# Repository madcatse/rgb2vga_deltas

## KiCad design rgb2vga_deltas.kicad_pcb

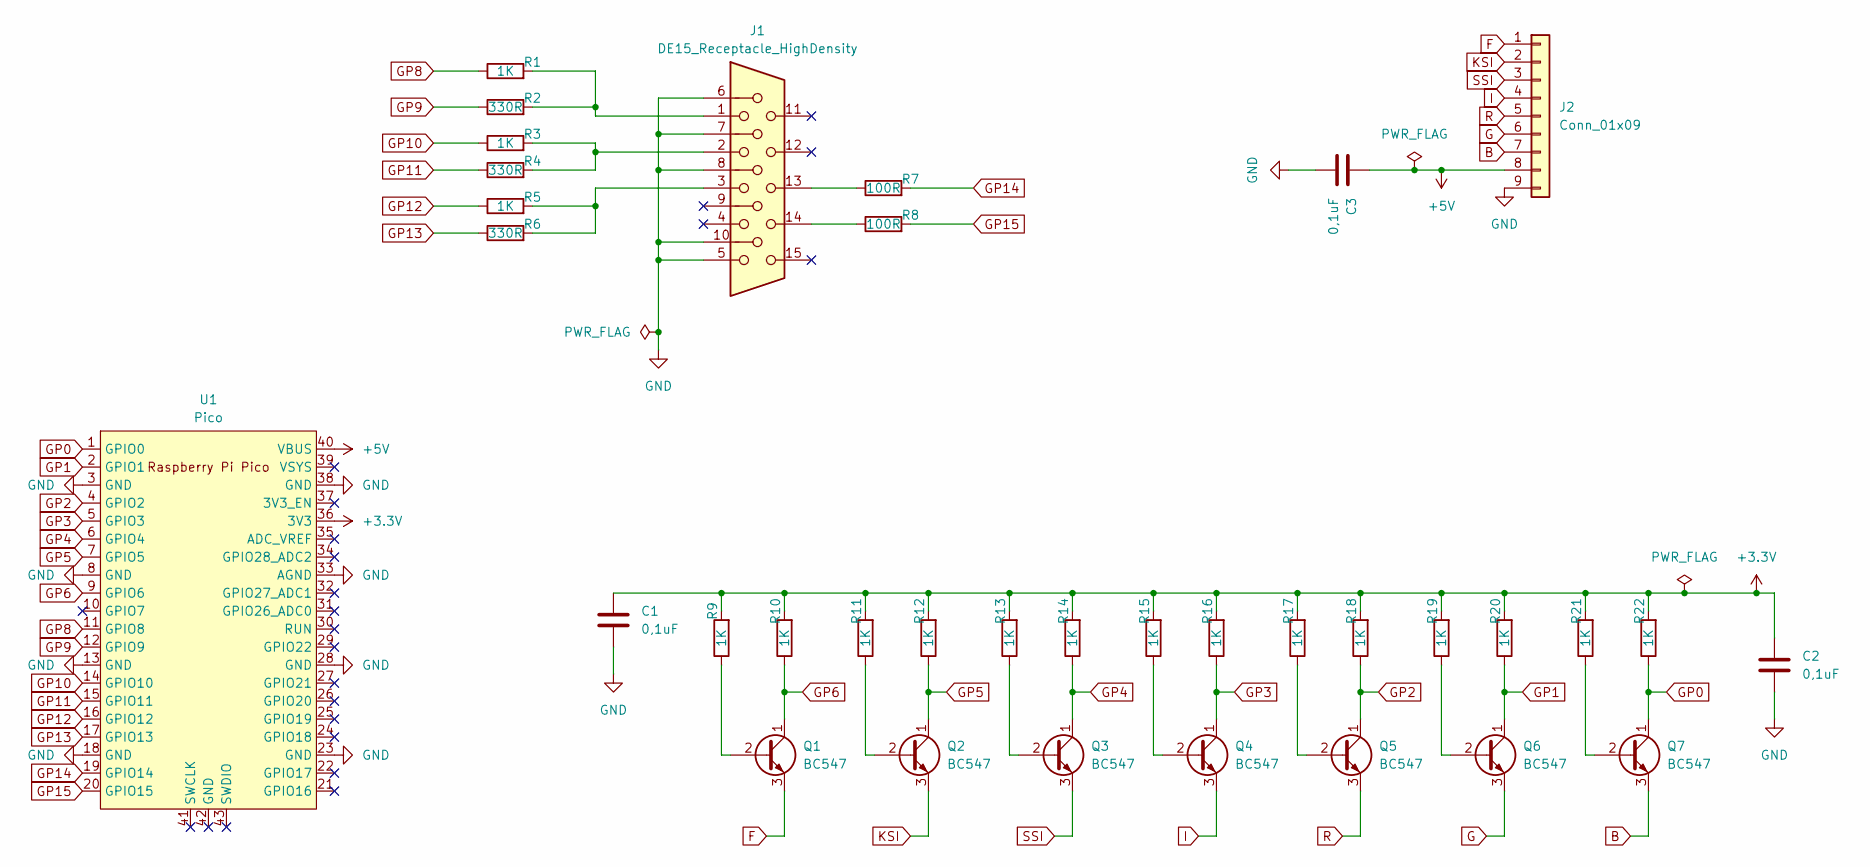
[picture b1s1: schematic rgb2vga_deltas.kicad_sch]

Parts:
C1, C2, C3: 0,1uF; C_Disc_D7.0mm_W2.5mm_P5.00mm
J1: DE15_Receptacle_HighDensity; DSUB-15-HD_Female_Horizontal_P2.29x1.98mm_EdgePinOffset3.03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
J2: Conn_01x09; PinHeader_1x09_P2.54mm_Vertical
Q1, Q2, Q3, Q4, Q5, Q6, Q7: BC547; TO-92_Inline
R1, R3, R5, R9, R10, R11, R12, R13, R14, R15, R16, R17, R18, R19, R20, R21, R22: 1K; R_Axial_DIN0207_L6.3mm_D2.5mm_P10.16mm_Horizontal
R2, R4, R6: 330R; R_Axial_DIN0207_L6.3mm_D2.5mm_P10.16mm_Horizontal
R7, R8: 100R; R_Axial_DIN0207_L6.3mm_D2.5mm_P10.16mm_Horizontal
U1: Pico; RPi_Pico_SMD_TH

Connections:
+3.3V: C1.1, C2.1, R9.2, R10.2, R11.2, R12.2, R13.2, R14.2, R15.2, R16.2, R17.2, R18.2, R19.2, R20.2, R21.2, R22.2, U1.36 (3V3)
+5V: C3.1, J2.8, U1.40 (VBUS)
B: J2.7, Q7.3 (E)
F: J2.1, Q1.3 (E)
G: J2.6, Q6.3 (E)
GND: C1.2, C2.2, C3.2, J1.5, J1.6, J1.7, J1.8, J1.10, J2.9, U1.3 (GND), U1.8 (GND), U1.13 (GND), U1.18 (GND), U1.23 (GND), U1.28 (GND), U1.33 (AGND), U1.38 (GND)
GP0: Q7.1 (C), R22.1, U1.1 (GPIO0)
GP1: Q6.1 (C), R20.1, U1.2 (GPIO1)
GP2: Q5.1 (C), R18.1, U1.4 (GPIO2)
GP3: Q4.1 (C), R16.1, U1.5 (GPIO3)
GP4: Q3.1 (C), R14.1, U1.6 (GPIO4)
GP5: Q2.1 (C), R12.1, U1.7 (GPIO5)
GP6: Q1.1 (C), R10.1, U1.9 (GPIO6)
GP8: R1.1, U1.11 (GPIO8)
GP9: R2.1, U1.12 (GPIO9)
GP10: R3.1, U1.14 (GPIO10)
GP11: R4.1, U1.15 (GPIO11)
GP12: R5.1, U1.16 (GPIO12)
GP13: R6.1, U1.17 (GPIO13)
GP14: R7.2, U1.19 (GPIO14)
GP15: R8.2, U1.20 (GPIO15)
I: J2.4, Q4.3 (E)
KSI: J2.2, Q2.3 (E)
unnamed: J1.1, R1.2, R2.2
unnamed: J1.2, R3.2, R4.2
unnamed: J1.3, R5.2, R6.2
unnamed: J1.13, R7.1
unnamed: J1.14, R8.1
unnamed: Q1.2 (B), R9.1
unnamed: Q2.2 (B), R11.1
unnamed: Q3.2 (B), R13.1
unnamed: Q4.2 (B), R15.1
unnamed: Q5.2 (B), R17.1
unnamed: Q6.2 (B), R19.1
unnamed: Q7.2 (B), R21.1
R: J2.5, Q5.3 (E)
SSI: J2.3, Q3.3 (E)

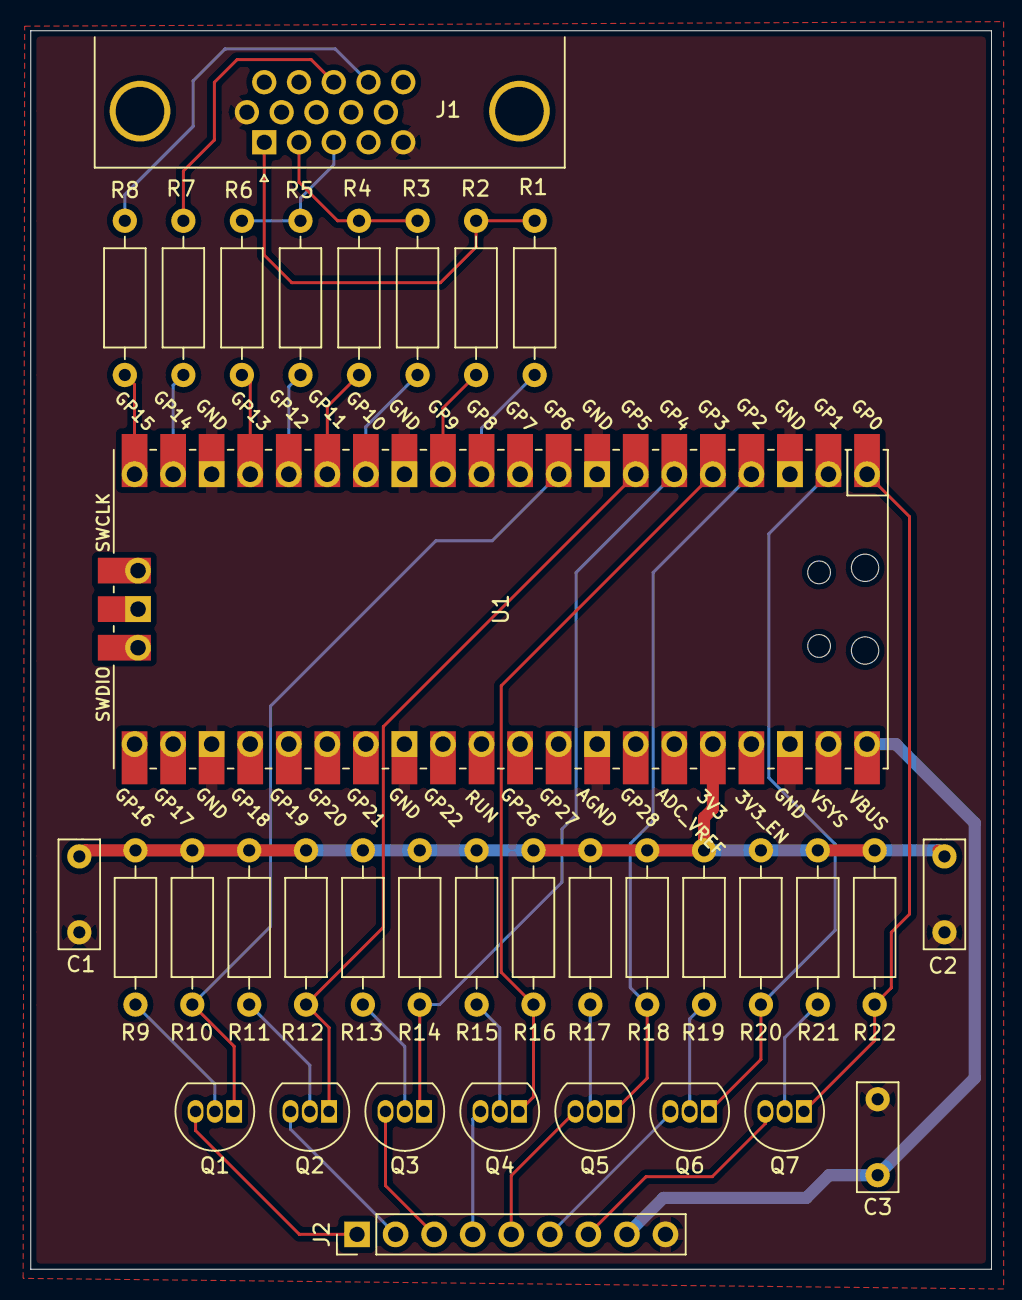
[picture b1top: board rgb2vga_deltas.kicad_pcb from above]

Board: 2 copper layers, 63.3 x 81.6 mm, 35 parts (0 on the bottom side), 37 nets.

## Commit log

2024-07-15 First version release
2024-07-15 Board routed
2026-05-26 Update Kicad 10
